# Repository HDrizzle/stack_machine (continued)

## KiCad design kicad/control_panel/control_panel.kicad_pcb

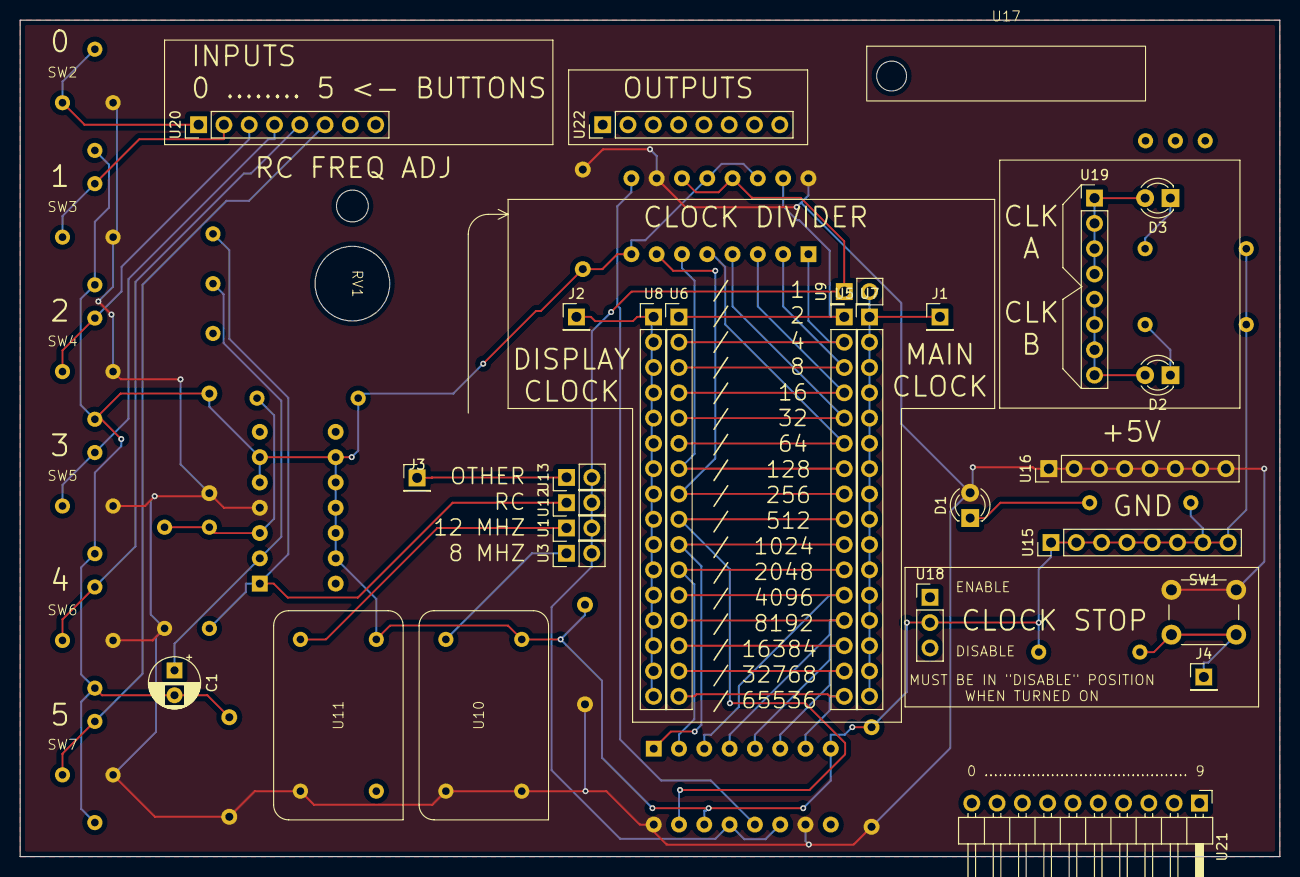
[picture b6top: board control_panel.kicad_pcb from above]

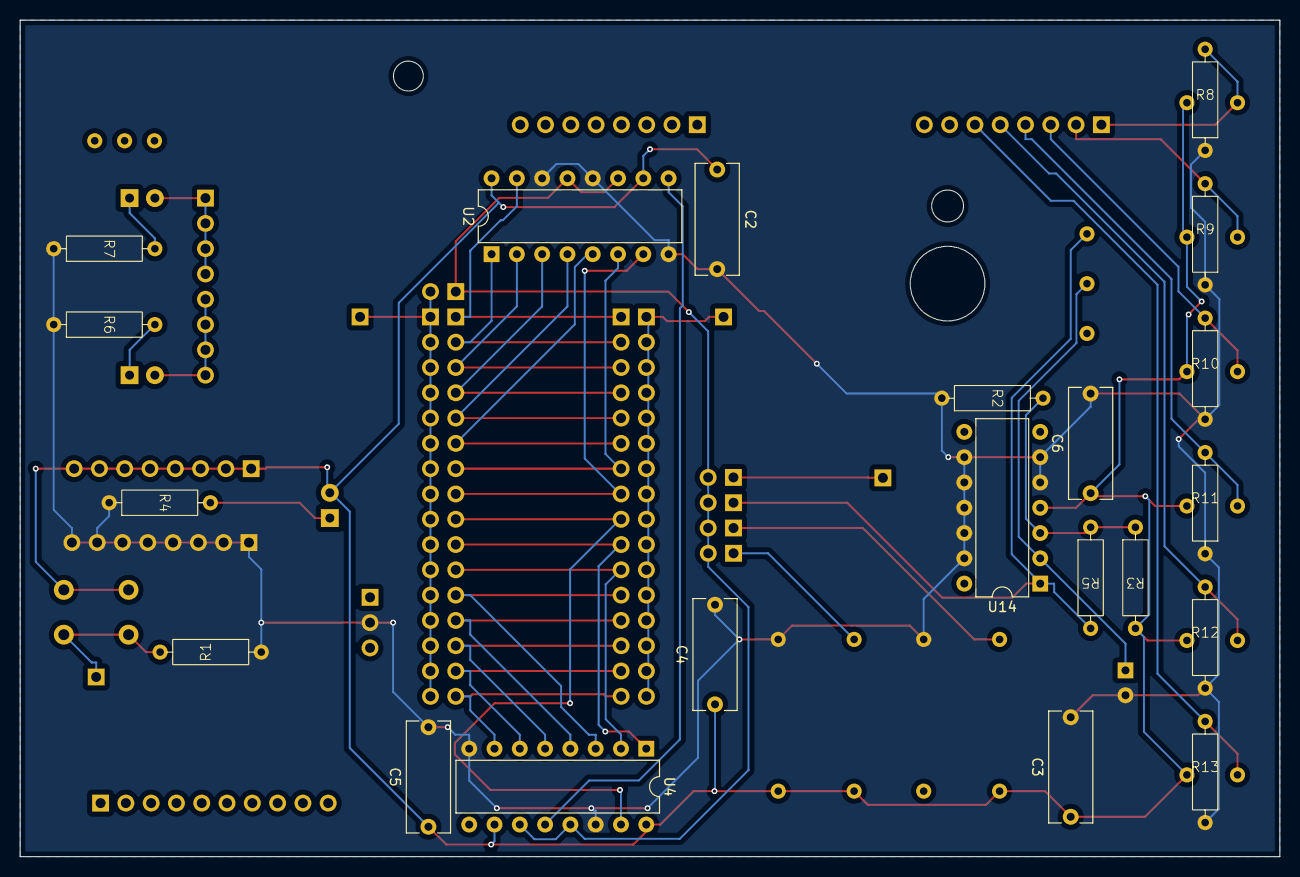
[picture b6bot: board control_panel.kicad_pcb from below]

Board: 2 copper layers, 126.5 x 84.0 mm, 56 parts (21 on the bottom side), 40 nets.

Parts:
C1: C; CP_Radial_D5.0mm_P2.50mm
C2, C3, C4, C5, C6: C; C_Rect_L11.0mm_W4.2mm_P10.00mm_MKT
D1, D2, D3: LED; LED_D3.0mm
J1, J2, J3, J4: Conn_01x01_Pin; PinHeader_1x01_P2.54mm_Vertical
R1, R2, R3, R4, R5, R6, R7, R8, R9, R10, R11, R12, R13: R; 0.4_pitch_resistor
RV1: R_Potentiometer; panel_mount_pot
SW1: SW_Push; SW_PUSH_6mm
SW2, SW3, SW4, SW5, SW6, SW7: SW_Push; 2_pin_button
U1, U3, U9, U12, U13: PinHeader_1x02_P2.54mm_Vertical
U2, U4: DIP-16_W7.62mm
U5, U6, U7, U8: PinHeader_1x16_P2.54mm_Vertical
U10, U11: crystal_dip_14
U14: DIP-14_W7.62mm
U15, U16, U19, U20, U22: PinHeader_1x08_P2.54mm_Vertical
U17: manual_clock_switch_side
U18: PinHeader_1x03_P2.54mm_Vertical
U21: PinHeader_1x10_P2.54mm_Horizontal

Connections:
unnamed: C2.1, C3.1, C4.1, C5.1, C6.1, D1.2 (A), R3.1, SW1.1, SW2.2, SW3.2, SW4.2, SW5.2, SW6.2, SW7.2, U2.10 (CCLR#), U2.16 (V+), U4.10 (CCLR#), U4.16 (V+), U10.1 (OE), U10.14 (V+), U11.14 (V+), U14.4 (V+), U16.1 (0), U16.2 (1), U16.3 (2), U16.4 (3), U16.5 (4), U16.6 (5), U16.7 (6), U16.8 (7)
unnamed: D1.1 (K), R4.1
unnamed: D2.2 (A), U19.5 (4), U19.6 (5), U19.7 (6), U19.8 (7)
unnamed: D2.1 (K), R6.1
unnamed: D3.2 (A), U19.1 (0), U19.2 (1), U19.3 (2), U19.4 (3)
unnamed: D3.1 (K), R7.1
unnamed: J1.1, U7.1 (0), U7.2 (1), U7.3 (2), U7.4 (3), U7.5 (4), U7.6 (5), U7.7 (6), U7.8 (7), U7.9 (8), U7.10 (9), U7.11 (10), U7.12 (11), U7.13 (12), U7.14 (13), U7.15 (14), U7.16 (15), U9.2 (B)
unnamed: J2.1, U8.1 (0), U8.2 (1), U8.3 (2), U8.4 (3), U8.5 (4), U8.6 (5), U8.7 (6), U8.8 (7), U8.9 (8), U8.10 (9), U8.11 (10), U8.12 (11), U8.13 (12), U8.14 (13), U8.15 (14), U8.16 (15)
unnamed: J3.1, U13.1 (A)
unnamed: J4.1, R1.1, SW1.2
unnamed: U1.1 (A), U11.8 (CLK)
unnamed: U1.2 (B), U2.11 (CCLK), U2.13 (RCLK), U3.2 (B), U4.11 (CCLK), U4.13 (RCLK), U9.1 (A), U12.2 (B), U13.2 (B)
unnamed: U2.15 (Q0), U5.1 (0), U6.1 (0)
unnamed: U2.1 (Q1), U5.2 (1), U6.2 (1)
unnamed: U2.2 (Q2), U5.3 (2), U6.3 (2)
unnamed: U2.3 (Q3), U5.4 (3), U6.4 (3)
unnamed: U2.4 (Q4), U5.5 (4), U6.5 (4)
unnamed: U2.5 (Q5), U5.6 (5), U6.6 (5)
unnamed: U2.6 (Q6), U5.7 (6), U6.7 (6)
unnamed: U2.7 (Q7), U5.8 (7), U6.8 (7)
unnamed: U2.9 (RCO#), U4.12 (CCKEN#)
unnamed: U4.15 (Q0), U5.9 (8), U6.9 (8)
unnamed: U4.1 (Q1), U5.10 (9), U6.10 (9)
unnamed: U4.2 (Q2), U5.11 (10), U6.11 (10)
unnamed: U4.3 (Q3), U5.12 (11), U6.12 (11)
unnamed: U4.4 (Q4), U5.13 (12), U6.13 (12)
unnamed: U4.5 (Q5), U5.14 (13), U6.14 (13)
unnamed: U4.6 (Q6), U5.15 (14), U6.15 (14)
unnamed: U4.7 (Q7), U5.16 (15), U6.16 (15)
unnamed: U3.1 (A), U10.8 (CLK)
unnamed: C1.2, C2.2, C3.2, C4.2, C5.2, C6.2, R1.2, R2.2, R4.2, R6.2, R7.2, R8.2, R9.2, R10.2, R11.2, R12.2, R13.2, U2.8 (GND), U2.12 (CCKEN#), U2.14 (OE#), U4.8 (GND), U4.14 (OE#), U10.7 (GND), U11.7 (GND), U14.5 (IN+_2), U14.6 (IN-_2), U14.9 (IN-_3), U14.10 (IN+_3), U14.11 (GND), U14.12 (IN+_4), U14.13 (IN-_4), U15.1 (0), U15.2 (1), U15.3 (2), U15.4 (3), U15.5 (4), U15.6 (5), U15.7 (6), U15.8 (7), U18.2 (2_(middle))
unnamed: R5.1, RV1.1, U12.1 (A), U14.1 (OUT_1)
unnamed: R2.1, R3.2, R5.2, U14.3 (IN+_1)
unnamed: C1.1, RV1.2, U14.2 (IN-_1)
unnamed: R8.1, SW2.1, U20.1 (0)
unnamed: R9.1, SW3.1, U20.2 (1)
unnamed: R10.1, SW4.1, U20.3 (2)
unnamed: R11.1, SW5.1, U20.4 (3)
unnamed: R12.1, SW6.1, U20.5 (4)
unnamed: R13.1, SW7.1, U20.6 (5)

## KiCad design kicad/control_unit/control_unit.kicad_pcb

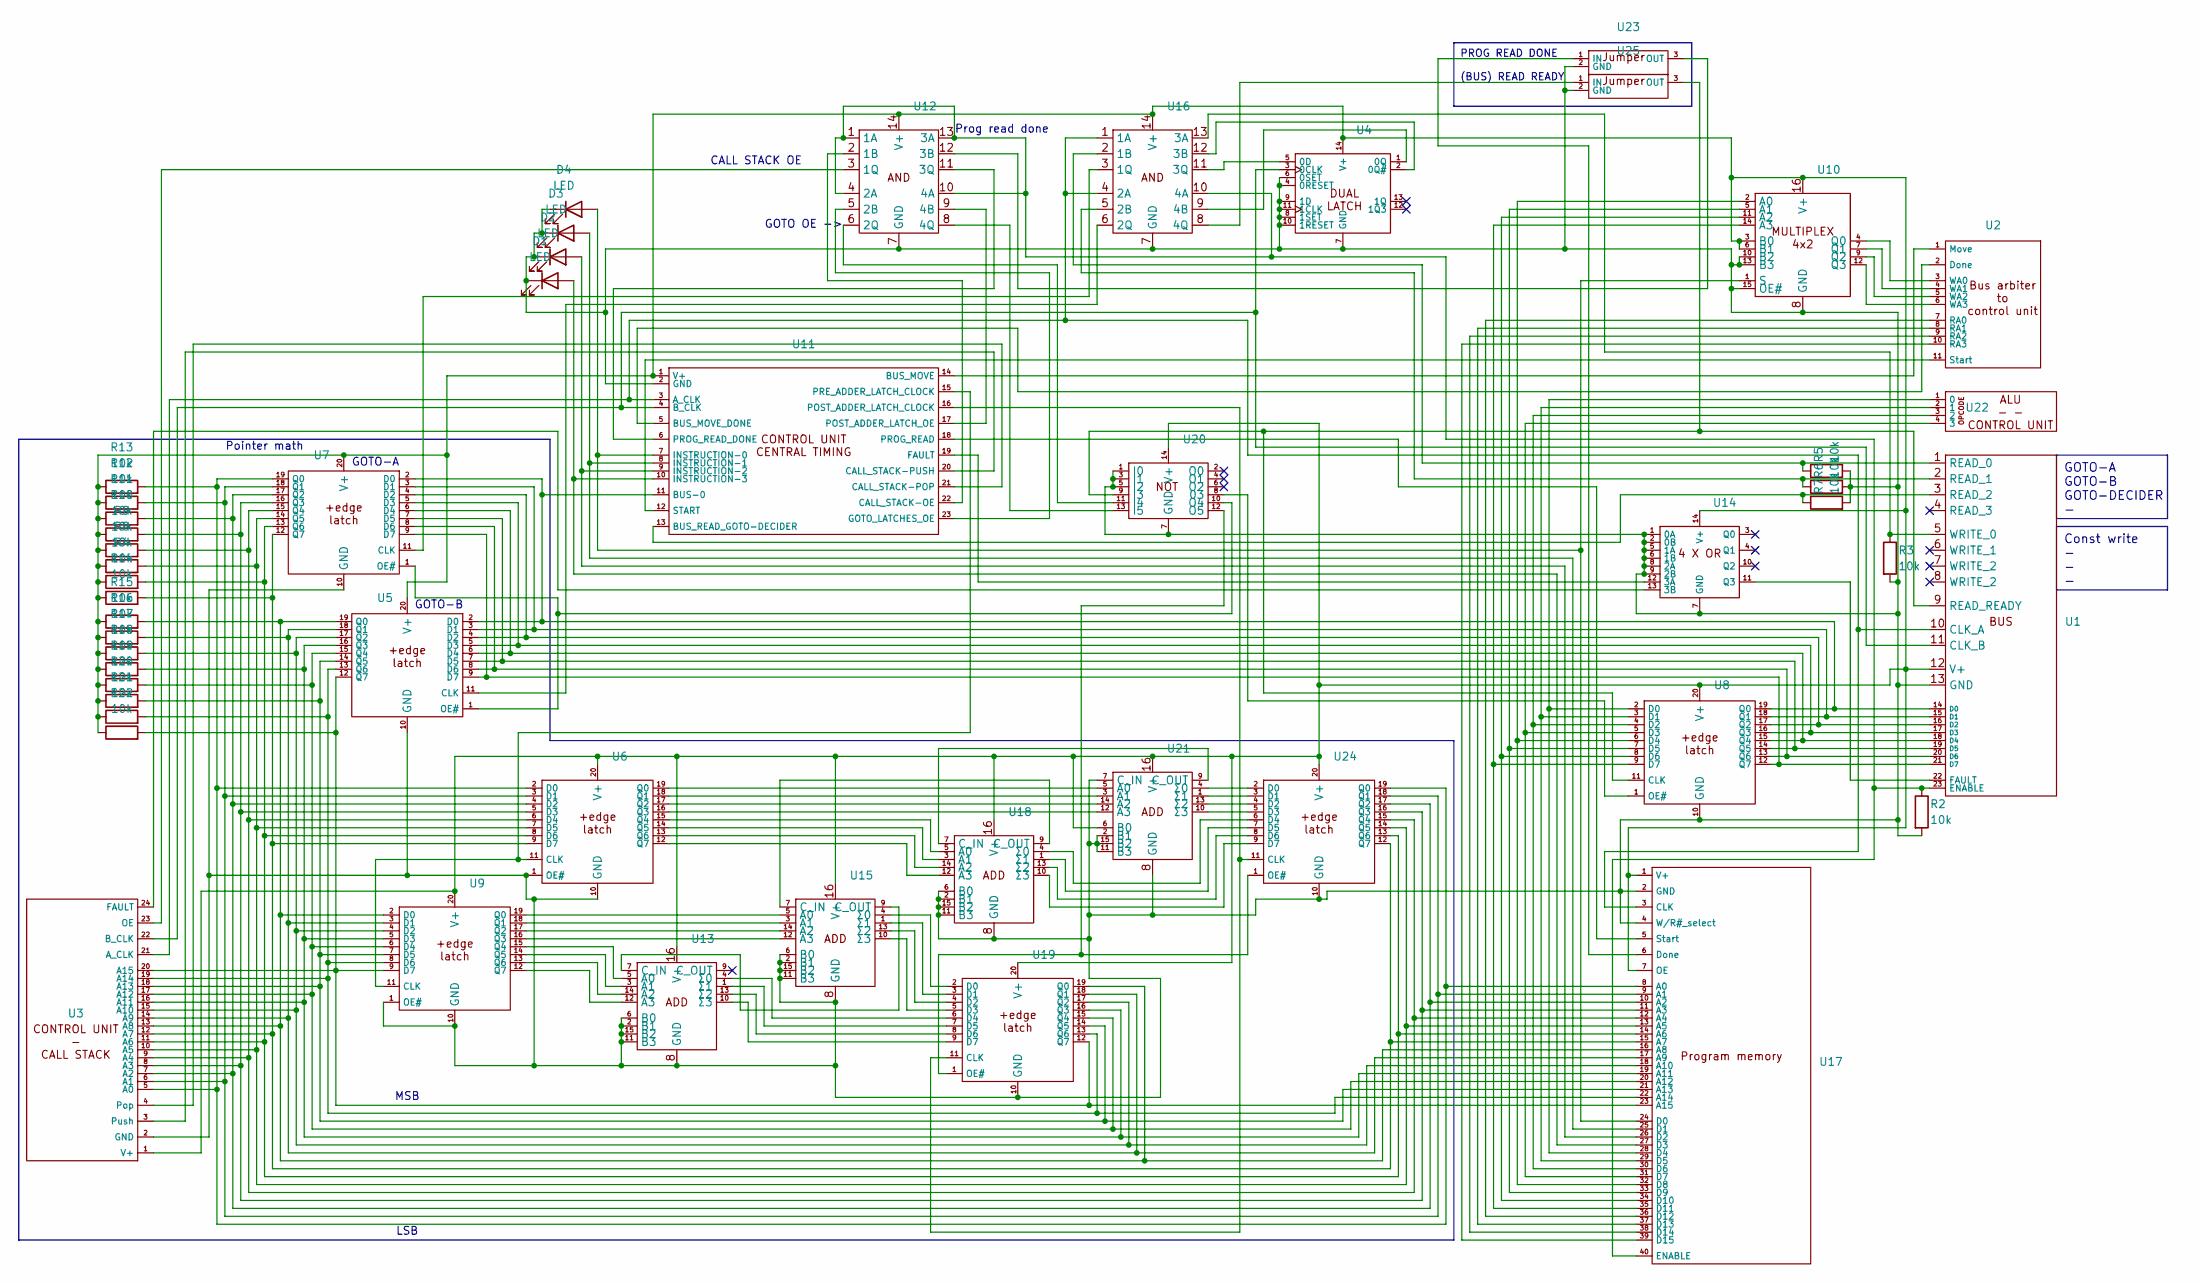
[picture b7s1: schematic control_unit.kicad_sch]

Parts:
D1, D2, D3, D4: LED; LED_D4.0mm
R2, R3, R4, R5, R6, R7, R8, R9, R10, R11, R12, R13, R14, R15, R16, R17, R18, R19, R20, R21, R22: 10k; 0.4_pitch_resistor
U1: PinHeader_1x23_P2.54mm_Vertical
U2: PinHeader_1x11_P2.54mm_Vertical
U3: PinHeader_1x24_P2.54mm_Vertical
U4, U12, U14, U16, U20: DIP-14_W7.62mm
U5, U6, U7, U8, U9, U19, U24: DIP-20_W7.62mm
U10, U13, U15, U18, U21: DIP-16_W7.62mm
U11: PinHeader_1x23_P2.54mm_Horizontal
U17: PinHeader_1x40_P2.54mm_Vertical
U22: PinHeader_1x04_P2.54mm_Vertical
U23, U25: jumper

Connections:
unnamed: D1.2 (A), U11.10 (INSTRUCTION-3), U17.27 (D3)
unnamed: D2.2 (A), U11.9 (INSTRUCTION-2), U17.26 (D2)
unnamed: D3.2 (A), U11.8 (INSTRUCTION-1), U17.25 (D1)
unnamed: D4.2 (A), U10.1 (S), U11.7 (INSTRUCTION-0), U17.24 (D0)
unnamed: U1.10 (CLK_A), U3.21 (A_CLK), U11.3 (A_CLK), U16.1 (1A), U16.4 (2A), U17.3 (CLK)
unnamed: U1.11 (CLK_B), U3.22 (B_CLK), U4.3 (0CLK), U11.4 (B_CLK)
unnamed: U1.14 (D0), U5.2 (D0), U7.2 (D0), U8.19 (Q0), U11.11 (BUS-0)
unnamed: U1.15 (D1), U5.3 (D1), U7.3 (D1), U8.18 (Q1)
unnamed: U1.16 (D2), U5.4 (D2), U7.4 (D2), U8.17 (Q2)
unnamed: U1.17 (D3), U5.5 (D3), U7.5 (D3), U8.16 (Q3)
unnamed: U1.18 (D4), U5.6 (D4), U7.6 (D4), U8.15 (Q4)
unnamed: U1.19 (D5), U5.7 (D5), U7.7 (D5), U8.14 (Q5)
unnamed: U1.20 (D6), U5.8 (D6), U7.8 (D6), U8.13 (Q6)
unnamed: U1.21 (D7), U5.9 (D7), U7.9 (D7), U8.12 (Q7)
unnamed: R2.1, U1.23 (ENABLE), U12.1 (1A), U12.4 (2A), U12.10 (4A), U12.13 (3A), U16.10 (4A), U17.40 (ENABLE)
unnamed: U1.22 (FAULT), U14.11 (Q3)
unnamed: R5.1, U1.1 (READ_0), U16.2 (1B)
unnamed: R6.1, U1.2 (READ_1), U16.5 (2B)
unnamed: R7.1, U1.3 (READ_2), U11.13 (BUS_READ_GOTO-DECIDER)
unnamed: U1.9 (READ_READY), U8.11 (CLK), U20.9 (I3), U25.3 (OUT)
unnamed: R3.1, U1.5 (WRITE_0), U16.13 (3A)
unnamed: U8.6 (D4), U10.2 (A0), U17.32 (D8)
unnamed: U8.7 (D5), U10.5 (A1), U17.33 (D9)
unnamed: U8.8 (D6), U10.11 (A2), U17.34 (D10)
unnamed: U8.9 (D7), U10.14 (A3), U17.35 (D11)
unnamed: U2.3 (WA0), U10.4 (Q0)
unnamed: U2.4 (WA1), U10.7 (Q1)
unnamed: U2.5 (WA2), U10.9 (Q2)
unnamed: U2.6 (WA3), U10.12 (Q3)
unnamed: U2.1 (Move), U11.14 (BUS_MOVE)
unnamed: U2.2 (Done), U11.5 (BUS_MOVE_DONE)
unnamed: U11.22 (CALL_STACK-OE), U12.2 (1B)
unnamed: U3.4 (Pop), U11.21 (CALL_STACK-POP)
unnamed: U3.3 (Push), U11.20 (CALL_STACK-PUSH)
unnamed: U11.19 (FAULT), U14.12 (3A)
unnamed: U11.23 (GOTO_LATCHES_OE), U12.5 (2B)
unnamed: U11.16 (POST_ADDER_LATCH_CLOCK), U19.11 (CLK), U24.11 (CLK)
unnamed: U11.17 (POST_ADDER_LATCH_OE), U12.9 (4B)
unnamed: U6.11 (CLK), U9.11 (CLK), U11.15 (PRE_ADDER_LATCH_CLOCK)
unnamed: U11.18 (PROG_READ), U17.5 (Read)
unnamed: U11.6 (PROG_READ_DONE), U12.11 (3Q)
unnamed: U2.11 (Start), U11.12 (START)
unnamed: U3.23 (OE), U12.3 (1Q)
unnamed: U12.6 (2Q), U20.11 (I4)
unnamed: U12.12 (3B), U23.3 (OUT)
unnamed: U12.8 (4Q), U20.13 (I5)
unnamed: U9.15 (Q4), U13.5 (A0)
unnamed: U9.14 (Q5), U13.3 (A1)
unnamed: U9.13 (Q6), U13.14 (A2)
unnamed: U9.12 (Q7), U13.12 (A3)
unnamed: U13.7 (C_IN), U15.9 (C_OUT)
unnamed: U13.4 (Σ0), U19.6 (D4)
unnamed: U13.1 (Σ1), U19.7 (D5)
unnamed: U13.13 (Σ2), U19.8 (D6)
unnamed: U13.10 (Σ3), U19.9 (D7)
unnamed: U3.24 (FAULT), U14.13 (3B)
unnamed: U9.19 (Q0), U15.5 (A0)
unnamed: U9.18 (Q1), U15.3 (A1)
unnamed: U9.17 (Q2), U15.14 (A2)
unnamed: U9.16 (Q3), U15.12 (A3)
unnamed: U15.7 (C_IN), U18.9 (C_OUT)
unnamed: U15.4 (Σ0), U19.2 (D0)
unnamed: U15.1 (Σ1), U19.3 (D1)
unnamed: U15.13 (Σ2), U19.4 (D2)
unnamed: U15.10 (Σ3), U19.5 (D3)
unnamed: U7.11 (CLK), U16.3 (1Q)
unnamed: U5.11 (CLK), U16.6 (2Q)
unnamed: U4.2 (0Q#), U16.12 (3B)
unnamed: U4.5 (0D), U16.11 (3Q)
unnamed: U4.1 (0Q), U16.9 (4B)
unnamed: U16.8 (4Q), U25.1 (IN)
unnamed: R13.2, U3.5 (A0), U6.2 (D0), U7.19 (Q0), U17.8 (A0), U24.19 (Q0)
unnamed: R12.2, U3.6 (A1), U6.3 (D1), U7.18 (Q1), U17.9 (A1), U24.18 (Q1)
unnamed: R11.2, U3.7 (A2), U6.4 (D2), U7.17 (Q2), U17.10 (A2), U24.17 (Q2)
unnamed: R10.2, U3.8 (A3), U6.5 (D3), U7.16 (Q3), U17.11 (A3), U24.16 (Q3)
unnamed: R9.2, U3.9 (A4), U6.6 (D4), U7.15 (Q4), U17.12 (A4), U24.15 (Q4)
unnamed: R8.2, U3.10 (A5), U6.7 (D5), U7.14 (Q5), U17.13 (A5), U24.14 (Q5)
unnamed: R4.2, U3.11 (A6), U6.8 (D6), U7.13 (Q6), U17.14 (A6), U24.13 (Q6)
unnamed: R14.2, U3.12 (A7), U6.9 (D7), U7.12 (Q7), U17.15 (A7), U24.12 (Q7)
unnamed: R15.2, U3.13 (A8), U5.19 (Q0), U9.2 (D0), U17.16 (A8), U19.19 (Q0)
unnamed: R16.2, U3.14 (A9), U5.18 (Q1), U9.3 (D1), U17.17 (A9), U19.18 (Q1)
unnamed: R17.2, U3.15 (A10), U5.17 (Q2), U9.4 (D2), U17.18 (A10), U19.17 (Q2)
unnamed: R18.2, U3.16 (A11), U5.16 (Q3), U9.5 (D3), U17.19 (A11), U19.16 (Q3)
unnamed: R19.2, U3.17 (A12), U5.15 (Q4), U9.6 (D4), U17.20 (A12), U19.15 (Q4)
unnamed: R20.2, U3.18 (A13), U5.14 (Q5), U9.7 (D5), U17.21 (A13), U19.14 (Q5)
unnamed: R21.2, U3.19 (A14), U5.13 (Q6), U9.8 (D6), U17.22 (A14), U19.13 (Q6)
unnamed: R22.2, U3.20 (A15), U5.12 (Q7), U9.9 (D7), U17.23 (A15), U19.12 (Q7)
unnamed: U8.2 (D0), U17.28 (D4), U22.1 (0)
unnamed: U8.3 (D1), U17.29 (D5), U22.2 (1)
unnamed: U8.4 (D2), U17.30 (D6), U22.3 (2)
unnamed: U8.5 (D3), U17.31 (D7), U22.4 (3)
unnamed: U2.7 (RA0), U17.36 (D12)
unnamed: U2.8 (RA1), U17.37 (D13)
unnamed: U2.9 (RA2), U17.38 (D14)
unnamed: U2.10 (RA3), U17.39 (D15)
unnamed: U17.6 (Done), U23.1 (IN)
unnamed: U6.15 (Q4), U18.5 (A0)
unnamed: U6.14 (Q5), U18.3 (A1)
unnamed: U6.13 (Q6), U18.14 (A2)
unnamed: U6.12 (Q7), U18.12 (A3)
unnamed: U18.7 (C_IN), U21.9 (C_OUT)
unnamed: U18.4 (Σ0), U24.6 (D4)
unnamed: U18.1 (Σ1), U24.7 (D5)
unnamed: U18.13 (Σ2), U24.8 (D6)
unnamed: U18.10 (Σ3), U24.9 (D7)
unnamed: U19.1 (OE#), U20.12 (O5), U24.1 (OE#)
unnamed: U8.1 (OE#), U20.8 (03)
unnamed: U5.1 (OE#), U7.1 (OE#), U20.10 (O4)
unnamed: U6.19 (Q0), U21.5 (A0)
unnamed: U6.18 (Q1), U21.3 (A1)
unnamed: U6.17 (Q2), U21.14 (A2)
unnamed: U6.16 (Q3), U21.12 (A3)
unnamed: U21.4 (Σ0), U24.2 (D0)
unnamed: U21.1 (Σ1), U24.3 (D1)
unnamed: U21.13 (Σ2), U24.4 (D2)
unnamed: U21.10 (Σ3), U24.5 (D3)

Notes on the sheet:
GOTO-A GOTO-B GOTO-DECIDER -
PROG READ DONE (BUS) READ READY
Const write - - -
GOTO OE ->
MSB
CALL STACK OE
GOTO-B
LSB
Prog read done
Pointer math
GOTO-A

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
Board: 2 copper layers, 50 parts (0 on the bottom side), 118 nets, no tracks yet.
